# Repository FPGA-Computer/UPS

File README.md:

UPS
===

This is the repository for my Switch Mode Power Supply modules & UPS schematic/PCB files.

Schematic tool: Eagle CAD 6.5.0
3D modelling: Sketchup 14.1 2014

Due to components availability, UPS design is provided as is.

Project page:
https://hw-by-design.blogspot.com/2018/08/vrm-power-supply-modules.html
http://hw-by-design.blogspot.com/2018/08/vrm-discrete-33v-buck-converter.html
http://hw-by-design.blogspot.com/2018/08/emergency-backup-power-and-wallwarts.html

Licensing:
Schematic: Creative Commons 4.0 Attribution-ShareAlike 4.0 International
PCB & Layout: Creative Commons 4.0 Attribution-NonCommercial
3D modelling: Creative Commons 4.0 Attribution-ShareAlike 4.0 International

Creative Commons 4.0 Attribution-NonCommercial:
See http://creativecommons.org/licenses/by-nc/4.0/

Creative Commons 4.0 Attribution-ShareAlike 4.0 International
See http://creativecommons.org/licenses/by-sa/4.0/

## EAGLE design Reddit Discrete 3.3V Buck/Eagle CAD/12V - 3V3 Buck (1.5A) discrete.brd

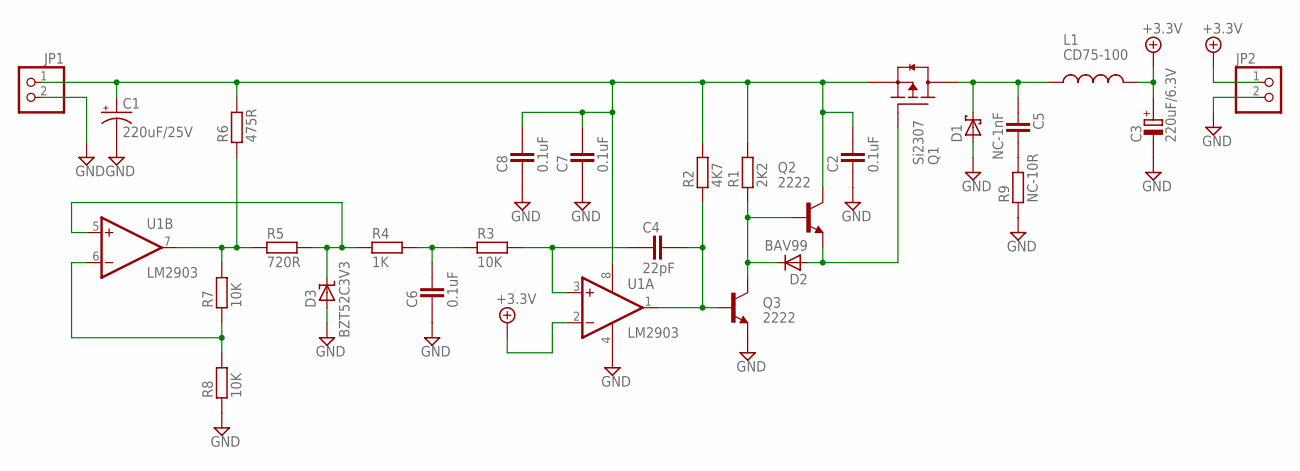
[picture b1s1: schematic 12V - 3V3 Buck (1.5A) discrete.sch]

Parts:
C1: 220uF/25V; PANASONIC_G
C2: 0.1uF; CAPC2012X145AN
C3: 220uF/6.3V; CAPMP7343X310N
C4: 22pF; CAPC1608X92N
C5: NC-1nF; CAPC1608X92N
C6, C7, C8: 0.1uF; CAPC1608X92N
D1: SCHOTTKY_SMC; DIOM7959X265N
D2: BAV99; SOT95P280X135-3N
D3: BZT52C3V3; SOD2514X100N
JP1, JP2: PINHD-1X2_2.54; 1X02
L1: CD75-100; CD75
Q1: Si2307; SOT95P280X135-3N
Q2, Q3: 2222; SOT95P280X135-3N
R1: 2K2; RESC1608X55N
R2: 4K7; RESC1608X55N
R3: 10K; RESC3115X70N
R4: 1K; RESC1608X55N
R5: 720R; RESC1608X55N
R6: 475R; RESC1608X55N
R7, R8: 10K; RESC1608X55N
R9: NC-10R; RESC1608X55N
U1: LM2903; SO08

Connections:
+3.3V: C3.+, JP2.1, L1.2, U1.2 (-IN)
GND: C1.-, C2.1, C3.-, C6.1, C7.1, C8.1, D1.A, D3.A, JP1.2, JP2.2, Q3.2 (E), R8.1, R9.1, U1.4 (V-)
unnamed: D2.3 (K), Q2.1 (B), Q3.3 (C), R1.1
unnamed: D2.1 (A), Q1.1 (G), Q2.2 (E)
unnamed: C4.2, Q3.1 (B), R2.1, U1.1 (OUT)
unnamed: C4.1, R3.2, U1.3 (+IN)
unnamed: C6.2, R3.1, R4.2
unnamed: C5.2, R9.2
unnamed: C1.+, C2.2, C7.2, C8.2, JP1.1, Q1.2 (S), Q2.3 (C), R1.2, R2.2, R6.2, U1.8 (V+)
unnamed: R5.1, R6.1, R7.2, U1.7 (OUT)
unnamed: R7.1, R8.2, U1.6 (-IN)
unnamed: D3.K, R4.1, R5.2, U1.5 (+IN)
VO-L: C5.1, D1.K, L1.1, Q1.3 (D)

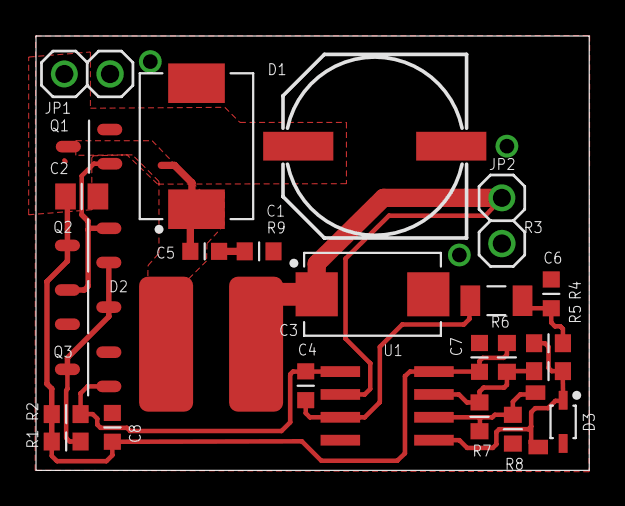
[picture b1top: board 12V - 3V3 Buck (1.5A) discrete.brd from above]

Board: 2 copper layers, 30.7 x 24.1 mm, 27 parts (0 on the bottom side), 13 nets.

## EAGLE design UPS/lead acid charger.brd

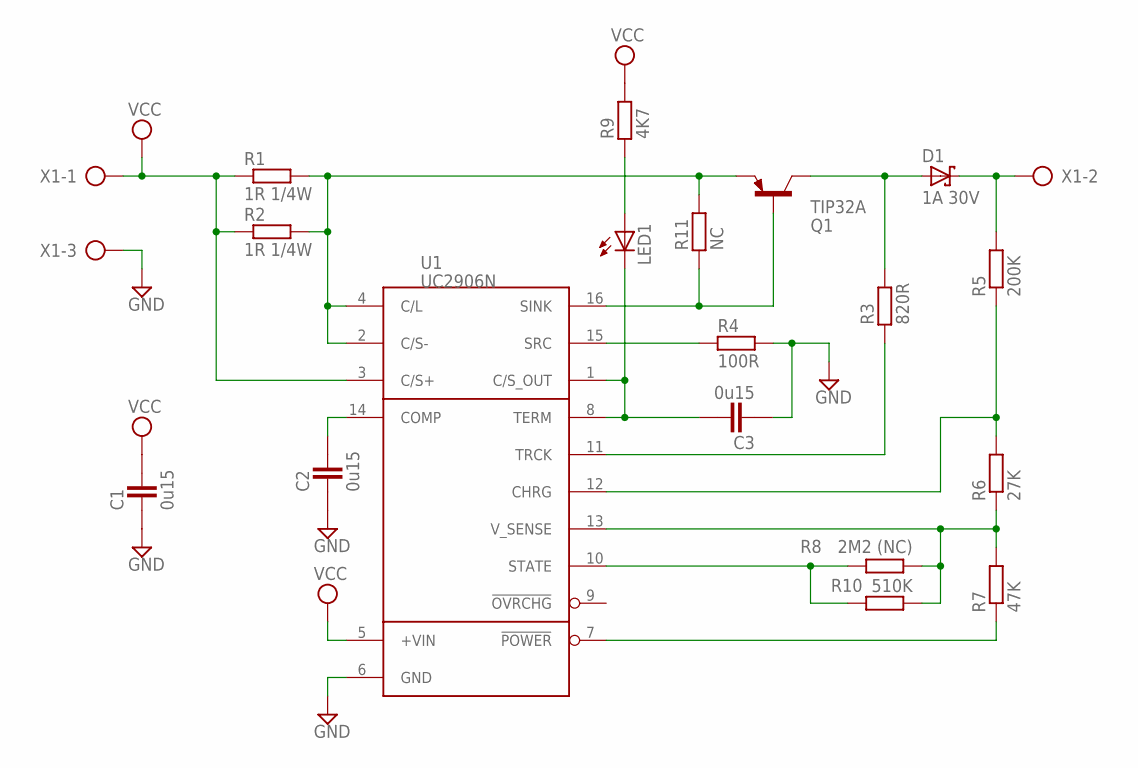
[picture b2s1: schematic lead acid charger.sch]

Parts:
C1, C2, C3: 0u15; CAP2012X70N
D1: 1A 30V; DIOM5436X265N
LED1: LED3MM
Q1: TIP32A; TO220
R1, R2: 1R 1/4W; 0207/10
R3: 820R; RESC3115X70N
R4: 100R; RESC2012X70N
R5: 200K; 0207/10
R6: 27K; 0207/10
R7: 47K; 0207/10
R8: 2M2 (NC); 0207/10
R9: 4K7; RESC2012X70N
R10: 510K; 0207/10
R11: NC; RESC1608X55N
U1: UC2906N; DIL16
X1: AK500/3; AK500-3

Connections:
GND: C1.1, C2.1, C3.1, R4.2, U1.6 (GND), X1.3
unnamed: C2.2, U1.14 (COMP)
unnamed: D1.K, R5.2, X1.2
unnamed: Q1.3 (E), R1.2, R2.2, R11.2, U1.2 (C/S-), U1.4 (C/L)
unnamed: C3.2, LED1.K (C), U1.1 (C/S_OUT), U1.8 (TERM)
unnamed: R7.1, U1.7 (!POWER)
unnamed: D1.A, Q1.2 (C), R3.2
unnamed: Q1.1 (B), R11.1, U1.16 (SINK)
unnamed: R3.1, U1.11 (TRCK)
unnamed: R4.1, U1.15 (SRC)
unnamed: R6.1, R7.2, R8.1, R10.1, U1.13 (V_SENSE)
unnamed: R5.1, R6.2, U1.12 (CHRG)
unnamed: R8.2, R10.2, U1.10 (STATE)
unnamed: LED1.A, R9.1
VCC: C1.2, R1.1, R2.1, R9.2, U1.3 (C/S+), U1.5 (+VIN), X1.1

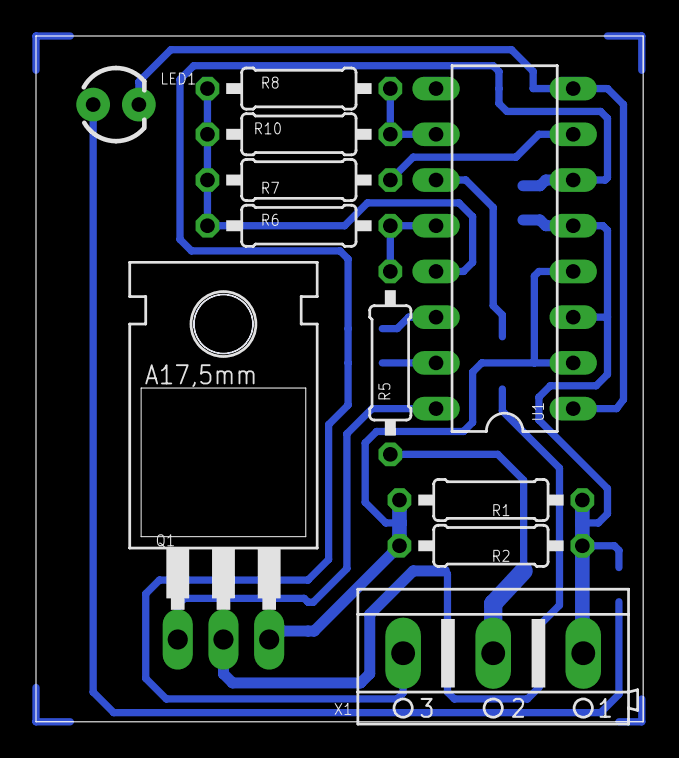
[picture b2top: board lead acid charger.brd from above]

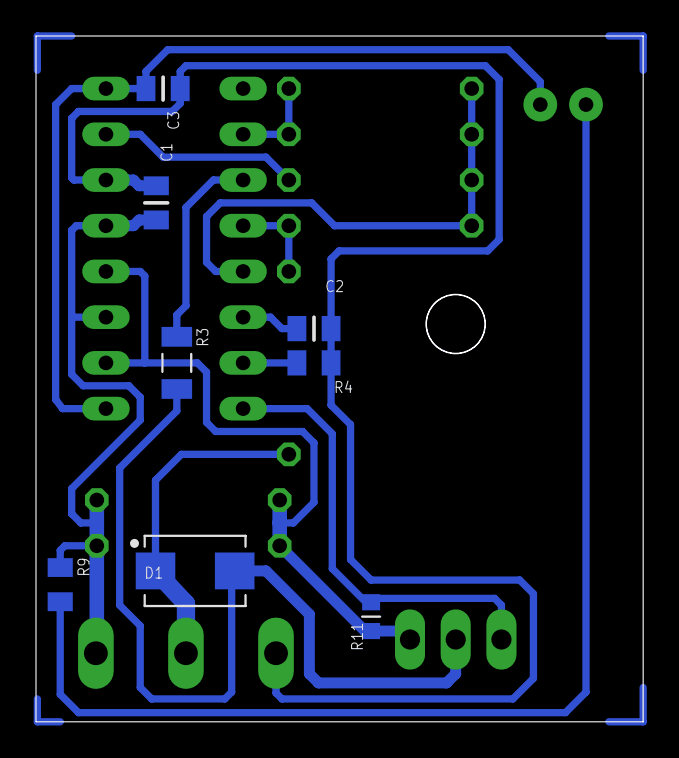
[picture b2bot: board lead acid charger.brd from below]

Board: 2 copper layers, 33.7 x 38.1 mm, 19 parts (8 on the bottom side), 15 nets.

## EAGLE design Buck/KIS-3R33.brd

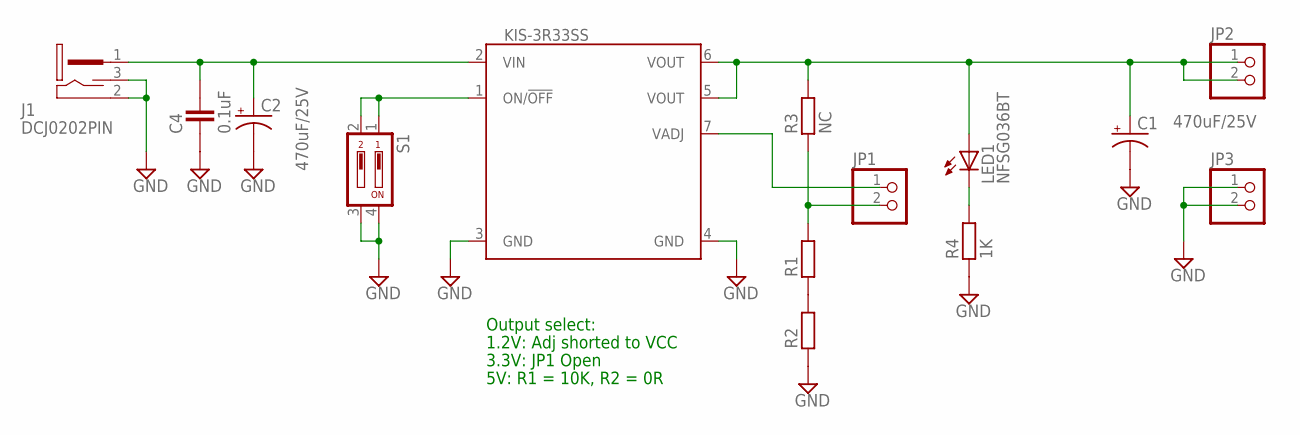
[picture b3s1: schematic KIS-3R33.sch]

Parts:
C1, C2: 470uF/25V; PANASONIC_G
C4: 0.1uF; CAP2012X70N
J1: DCJ0202PIN; PJ-102A
JP1: PINHD-1X2_2.54-SMD; 1X02SMD
JP2, JP3: PINHD-1X2_2.54; 1X02
LED1: NFSG036BT
R1, R2: RESISTOR_1206; RESC3115X70N
R3: NC; RESC3115X70N
R4: 1K; RESC1608X55N
S1: DIP02YL
U1: KIS-3R33SS; KIS-3R33S-SMT

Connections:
GND: C1.-, C2.-, C4.1, J1.2 (3), J1.3 (2), JP3.1, JP3.2, R2.1, R4.1, S1.3, S1.4, U1.3 (GND), U1.4 (GND)
unnamed: C1.+, JP2.1, JP2.2, LED1.A, R3.2, U1.5 (VOUT), U1.6 (VOUT)
unnamed: C2.+, C4.2, J1.1, U1.2 (VIN)
unnamed: JP1.1, U1.7 (VADJ)
unnamed: R1.1, R2.2
unnamed: JP1.2, R1.2, R3.1
unnamed: LED1.C, R4.2
unnamed: S1.1, S1.2, U1.1 (ON/!OFF)

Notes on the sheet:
5V: R1 = 10K, R2 = 0R
3.3V: JP1 Open
1.2V: Adj shorted to VCC
Output select:

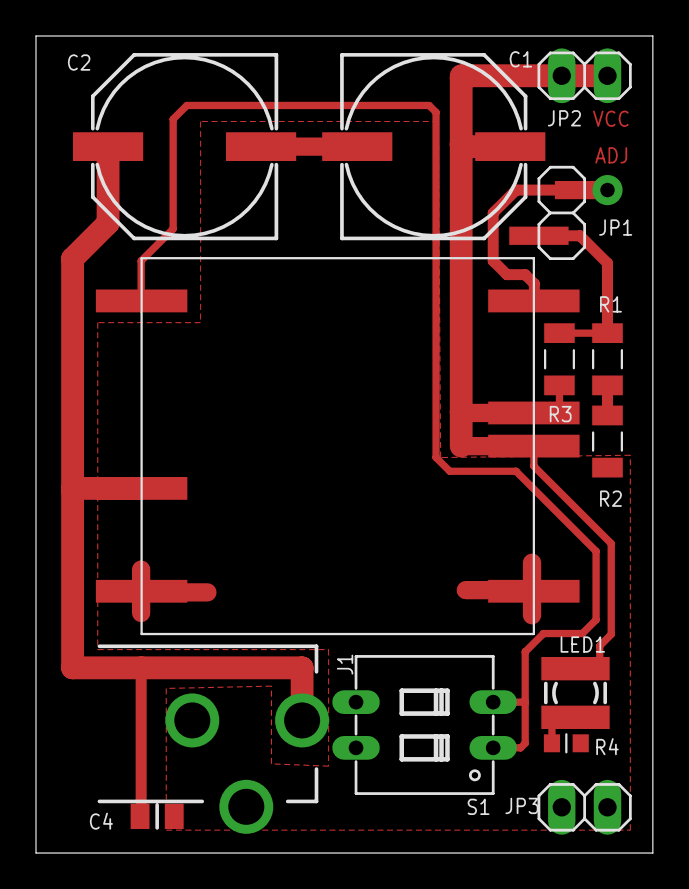
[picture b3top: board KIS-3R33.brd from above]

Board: 2 copper layers, 34.3 x 45.4 mm, 14 parts (0 on the bottom side), 8 nets.

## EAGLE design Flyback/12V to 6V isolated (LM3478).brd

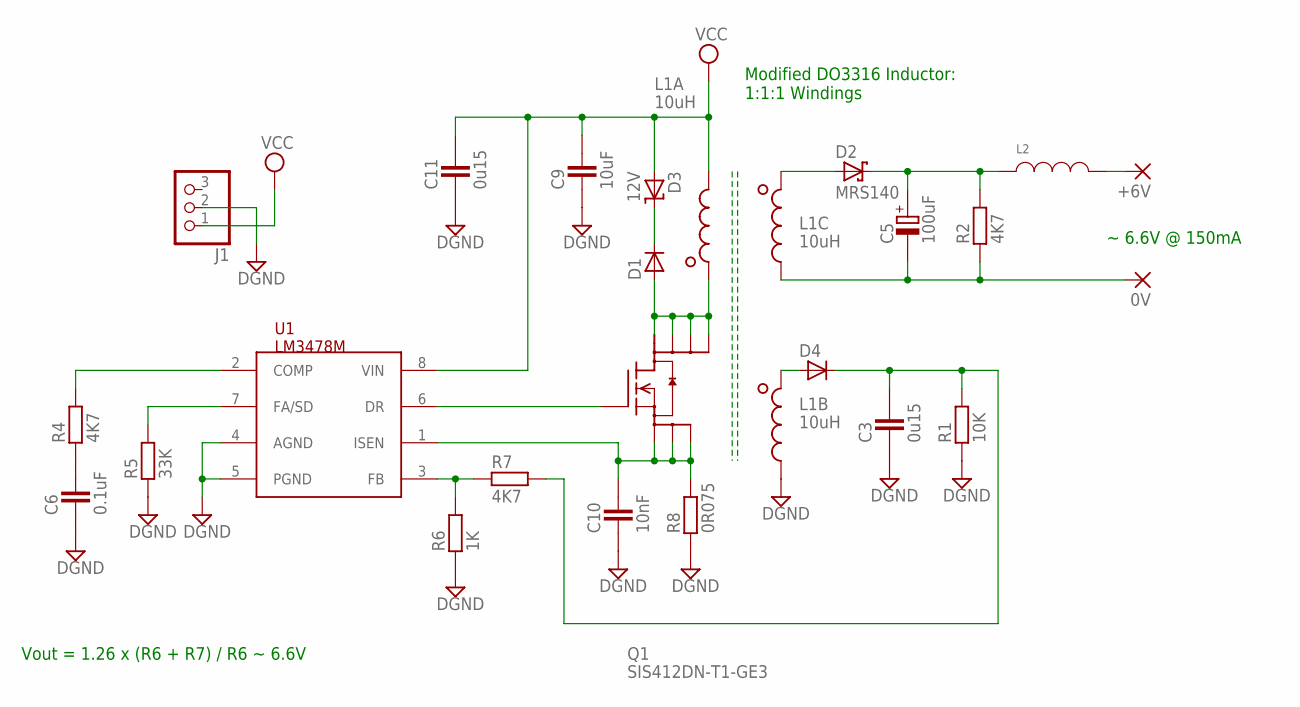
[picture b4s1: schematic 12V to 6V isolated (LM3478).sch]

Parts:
0V: SMD2; SMD1,27-2,54
+6V: SMD2; SMD1,27-2,54
C3, C11: 0u15; CAP2012X70N
C5: 100uF; CAPMP7343X310N
C6: 0.1uF; CAPC1608X92N
C9: 10uF; CAPC3225X168N
C10: 10nF; CAPC1608X92N
D1, D4: DIODE_SOT-23; SOT95P280X135-3N
D2: MRS140; DIOM5436X265N
D3: 12V; SOT95P280X135-3N
J1: PINHD-1X3; 1X03
L1: 10uH; DO3316P-3
L2: INDUCTOR_1812; INDC4532X175N
Q1: SIS412DN-T1-GE3; POWER-PAK1212
R1: 10K; RESC2012X70N
R2, R7: 4K7; RESC2012X70N
R4: 4K7; RESC1608X55N
R5: 33K; RESC1608X55N
R6: 1K; RESC2012X70N
R8: 0R075; RESC6432X70N
U1: LM3478M; MSOP8

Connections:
DGND: C3.1, C6.1, C9.1, C10.1, C11.1, J1.2, L1.4 (2), R1.1, R5.1, R6.1, R8.1, U1.4 (AGND), U1.5 (PGND)
unnamed: R4.2, U1.2 (COMP)
unnamed: D1.3 (K), D3.3 (K)
unnamed: C6.2, R4.1
unnamed: R5.2, U1.7 (FA/SD)
unnamed: D4.1 (A), L1.3 (1)
unnamed: Q1.4 (G), U1.6 (DR)
unnamed: C3.2, D4.3 (K), R1.2, R7.2
unnamed: C5.+, D2.K, L2.1, R2.2
unnamed: R6.2, R7.1, U1.3 (FB)
unnamed: 0V.1, C5.-, L1.6 (2), R2.1
unnamed: D1.1 (A), L1.1, Q1.5 (D1), Q1.6 (D2), Q1.7 (D3), Q1.8 (D4)
unnamed: D2.A, L1.5 (1)
unnamed: +6V.1, L2.2
unnamed: C10.2, Q1.1 (S1), Q1.2 (S2), Q1.3 (S3), R8.2, U1.1 (ISEN)
VCC: C9.2, C11.2, D3.1 (A), J1.1, L1.2, U1.8 (VIN)

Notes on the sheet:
Vout = 1.26 x (R6 + R7) / R6 ~ 6.6V
~ 6.6V @ 150mA
Modified DO3316 Inductor: 1:1:1 Windings

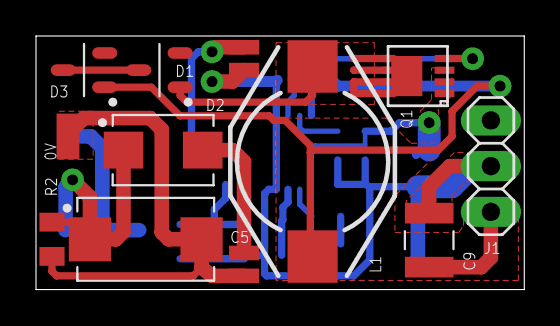
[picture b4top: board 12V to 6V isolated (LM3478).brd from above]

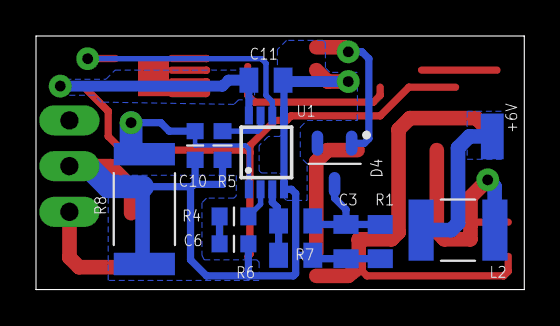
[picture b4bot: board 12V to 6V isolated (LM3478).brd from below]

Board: 2 copper layers, 27.1 x 14.1 mm, 24 parts (14 on the bottom side), 16 nets.

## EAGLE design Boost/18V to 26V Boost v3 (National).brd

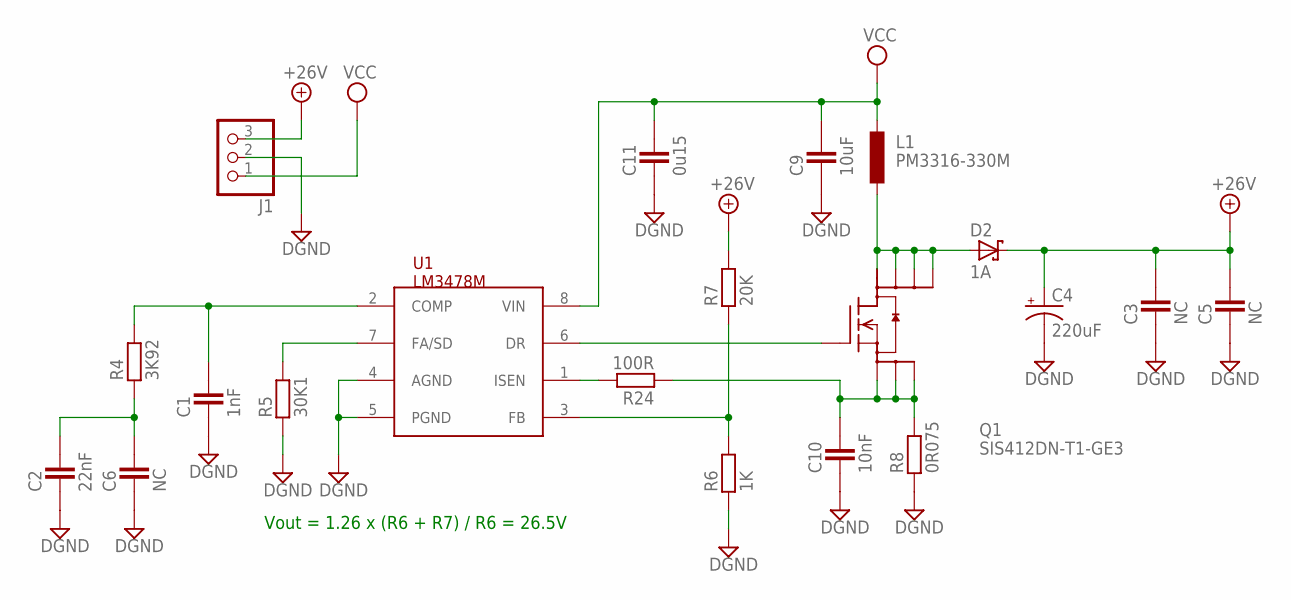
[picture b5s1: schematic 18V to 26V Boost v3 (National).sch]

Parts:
C1: 1nF; CAP2012X70N
C2: 22nF; CAPC1608X92N
C3, C5: NC; CAPC3225X168N
C4: 220uF; PANASONIC_G
C6: NC; CAPC1608X92N
C9: 10uF; CAPC3225X168N
C10: 10nF; CAPC1608X92N
C11: 0u15; CAP2012X70N
D2: 1A; DIOM5436X265N
J1: PINHD-1X3; 1X03
L1: PM3316-330M; DO3316P
Q1: SIS412DN-T1-GE3; POWER-PAK1212
R4: 3K92; RESC1608X55N
R5: 30K1; RESC1608X55N
R6: 1K; RESC1608X55N
R7: 20K; RESC1608X55N
R8: 0R075; RESC6432X70N
R24: 100R; RESC1608X55N
U1: LM3478M; MSOP08

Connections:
+26V: C3.2, C4.+, C5.2, D2.K, J1.3, R7.2
DGND: C1.1, C2.1, C3.1, C4.-, C5.1, C6.1, C9.1, C10.1, C11.1, J1.2, R5.1, R6.1, R8.1, U1.4 (AGND), U1.5 (PGND)
unnamed: C1.2, R4.2, U1.2 (COMP)
unnamed: C2.2, C6.2, R4.1
unnamed: R5.2, U1.7 (FA/SD)
unnamed: Q1.4 (G), U1.6 (DR)
unnamed: R6.2, R7.1, U1.3 (FB)
unnamed: C10.2, Q1.1 (S1), Q1.2 (S2), Q1.3 (S3), R8.2, R24.1
unnamed: D2.A, L1.2, Q1.5 (D1), Q1.6 (D2), Q1.7 (D3), Q1.8 (D4)
unnamed: R24.2, U1.1 (ISEN)
VCC: C9.2, C11.2, J1.1, L1.1, U1.8 (VIN)

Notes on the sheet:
Vout = 1.26 x (R6 + R7) / R6 = 26.5V

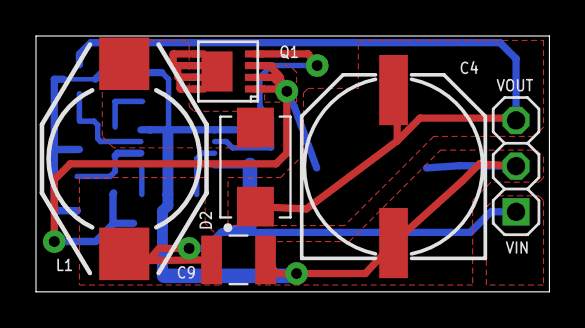
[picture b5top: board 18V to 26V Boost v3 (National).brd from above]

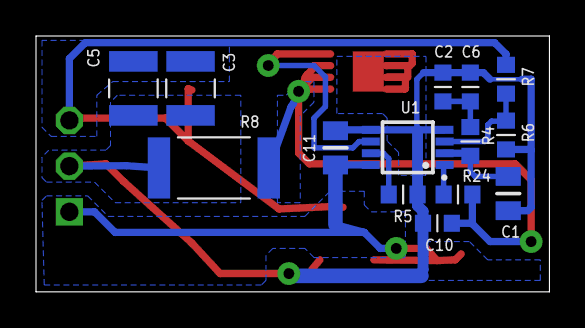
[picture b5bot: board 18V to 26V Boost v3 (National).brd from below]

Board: 2 copper layers, 28.5 x 14.2 mm, 20 parts (14 on the bottom side), 11 nets.

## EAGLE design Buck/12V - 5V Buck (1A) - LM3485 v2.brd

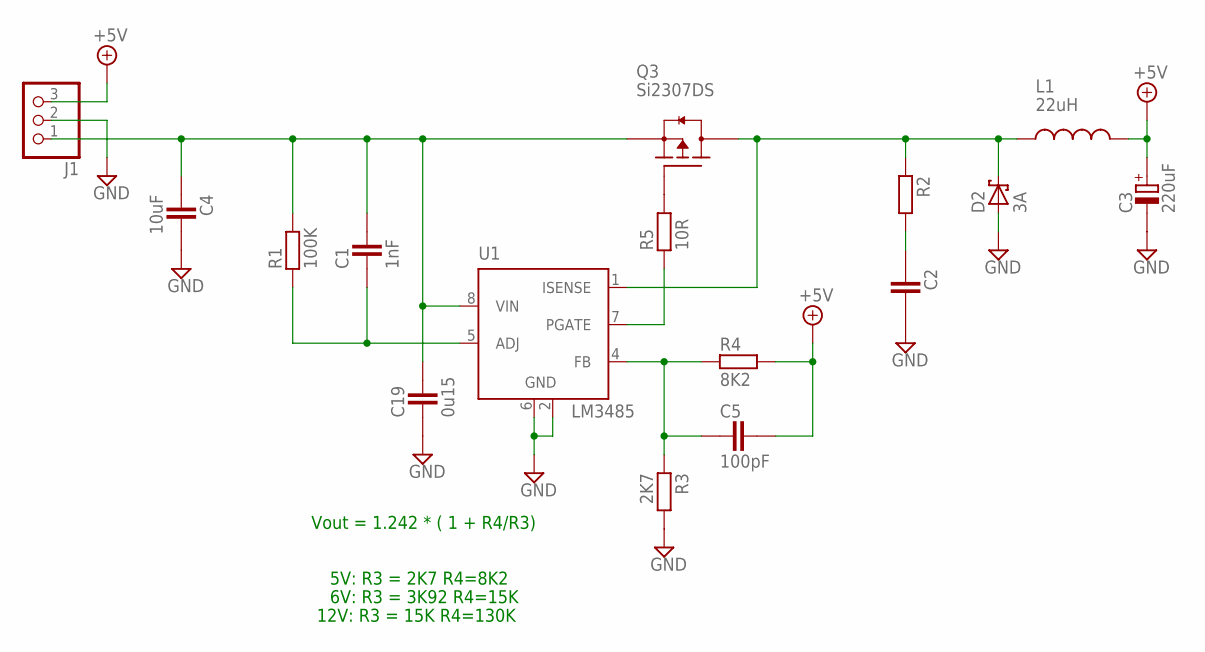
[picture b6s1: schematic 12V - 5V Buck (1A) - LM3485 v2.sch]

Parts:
C1: 1nF; CAP2012X70N
C2: CAPACITOR_0805N; CAP2012X70N
C3: 220uF; CAPMP7343X310N
C4: 10uF; CAPC3225X168N
C5: 100pF; CAP2012X70N
C19: 0u15; CAPC1608X92N
D2: 3A; DIOM7959X265N
J1: PINHD-1X3; 1X03
L1: 22uH; DO3316P
Q3: Si2307DS; SOT95P280X135-3N
R1: 100K; RESC1608X55N
R2: RESISTOR_0603; RESC1608X55N
R3: 2K7; RESC2012X70N
R4: 8K2; RESC2012X70N
R5: 10R; RESC1608X55N
U1: LM3485; MSOP08

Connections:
+5V: C3.+, C5.2, J1.3, L1.2, R4.2
+12V: C1.2, C4.1, C19.2, J1.1, Q3.2 (S), R1.2, U1.8 (VIN)
GND: C2.2, C3.-, C4.2, C19.1, D2.A, J1.2, R3.2, U1.2 (GND), U1.6 (GND)
unnamed: C5.1, R3.1, R4.1, U1.4 (FB)
unnamed: R5.1, U1.7 (PGATE)
unnamed: C1.1, R1.1, U1.5 (ADJ)
unnamed: C2.1, R2.2
unnamed: Q3.1 (G), R5.2
VO-L: D2.K, L1.1, Q3.3 (D), R2.1, U1.1 (ISENSE)

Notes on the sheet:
Vout = 1.242 * ( 1 + R4/R3)
5V: R3 = 2K7 R4=8K2
12V: R3 = 15K R4=130K
6V: R3 = 3K92 R4=15K

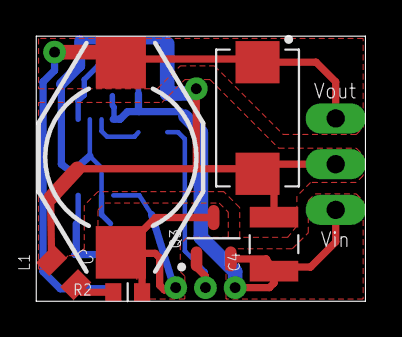
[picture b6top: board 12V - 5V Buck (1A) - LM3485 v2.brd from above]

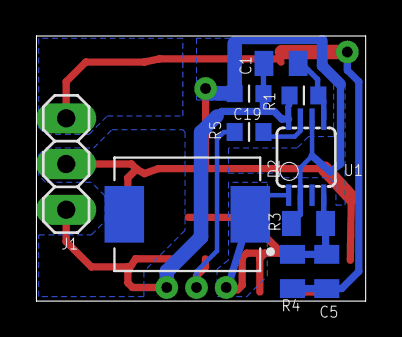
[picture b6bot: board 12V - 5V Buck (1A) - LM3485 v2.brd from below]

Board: 2 copper layers, 18.3 x 14.7 mm, 16 parts (10 on the bottom side), 9 nets.

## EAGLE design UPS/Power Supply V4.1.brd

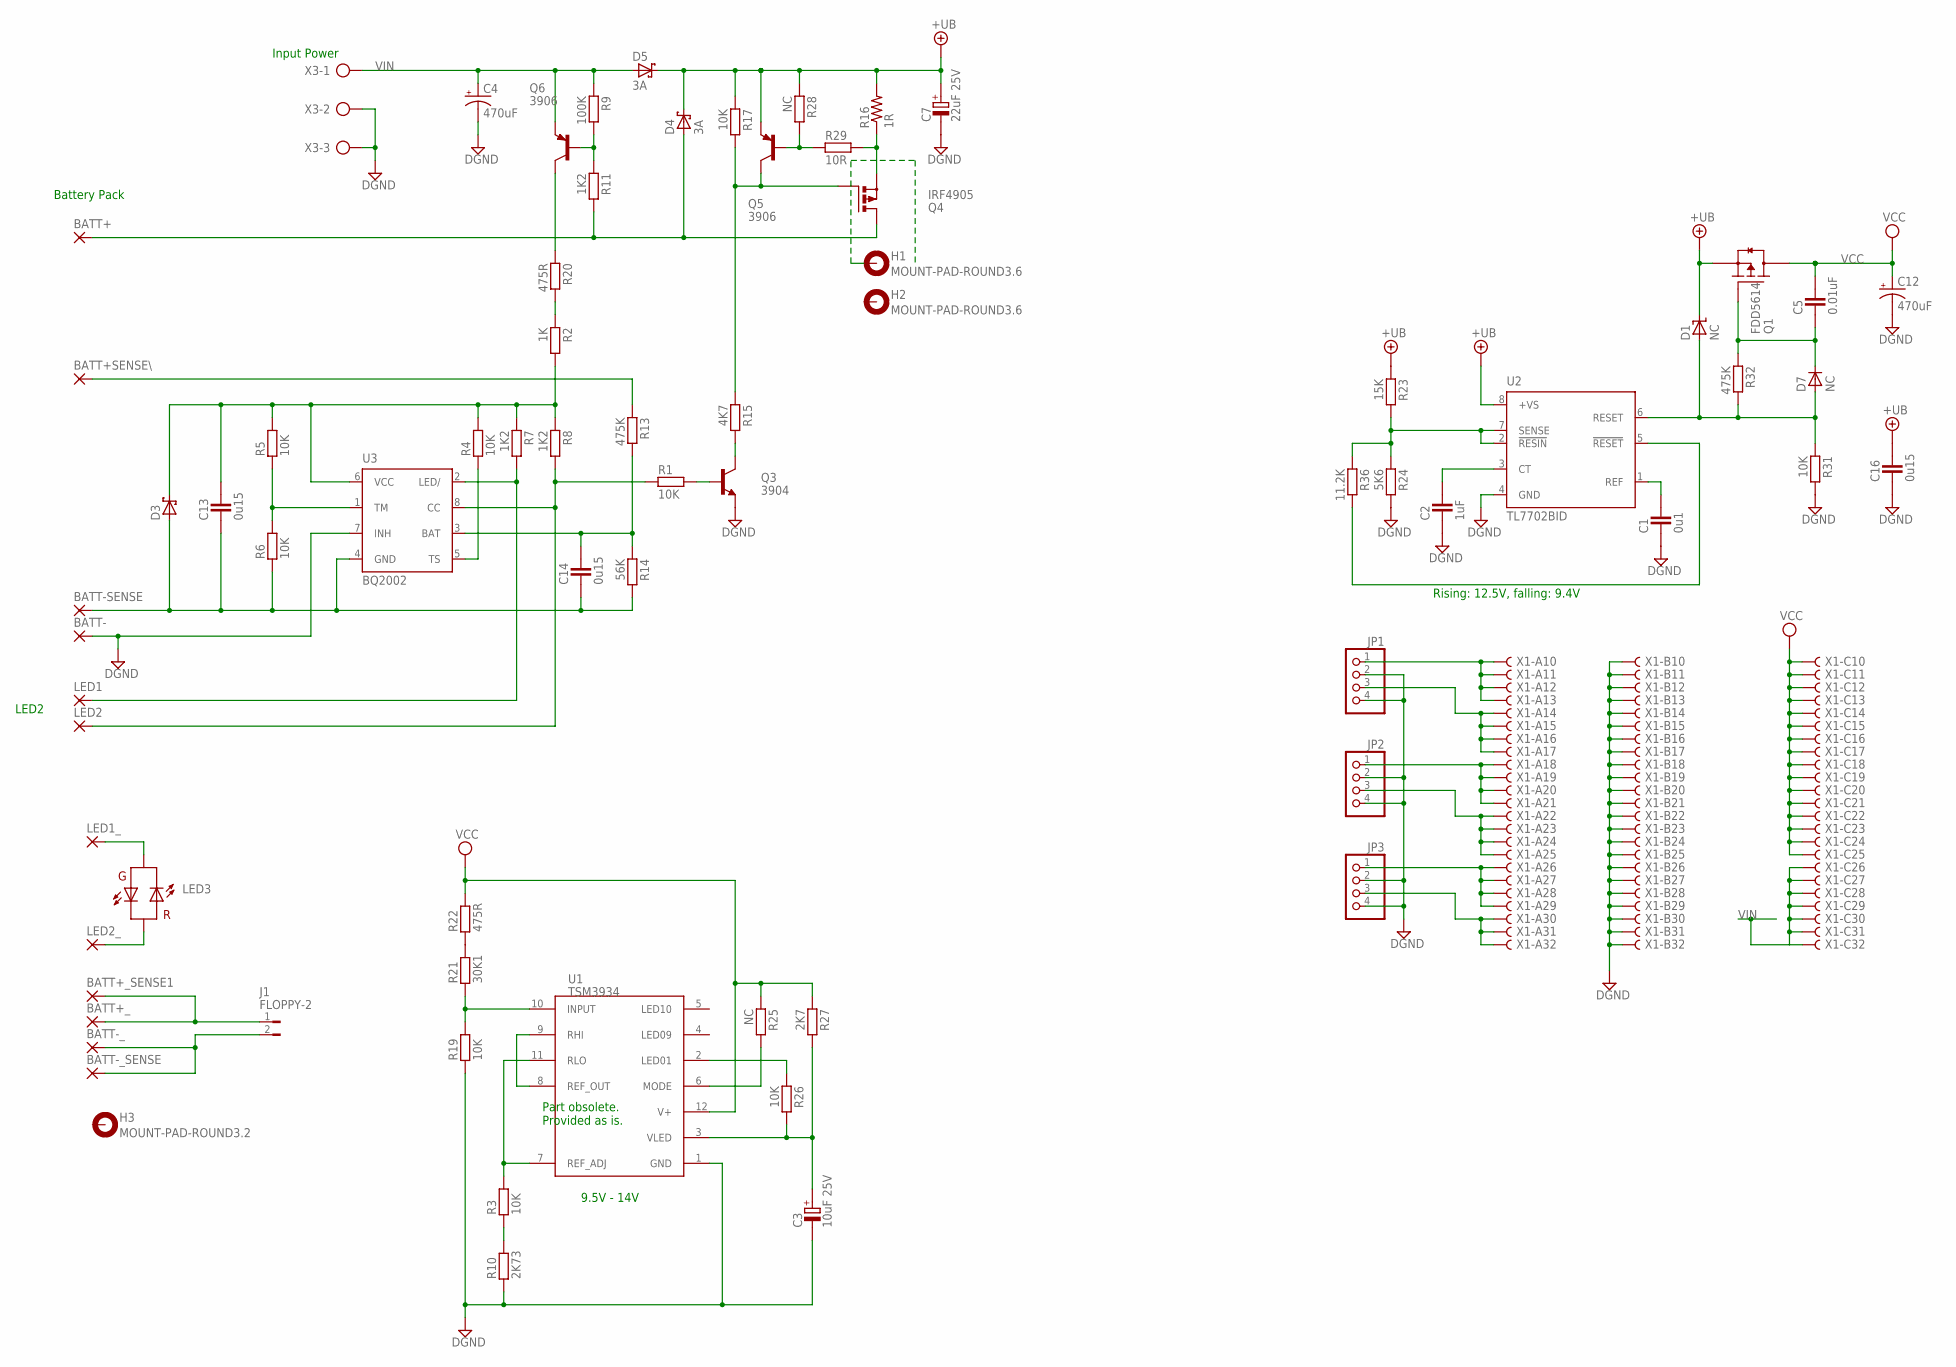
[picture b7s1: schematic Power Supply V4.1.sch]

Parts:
BATT+: SMD5; SMD2,54-5,08
BATT+SENSE\: SMD5; SMD2,54-5,08
BATT+_: SMD5; SMD2,54-5,08
BATT+_SENSE1: SMD5; SMD2,54-5,08
BATT-: SMD5; SMD2,54-5,08
BATT-SENSE: SMD5; SMD2,54-5,08
BATT-_: SMD5; SMD2,54-5,08
BATT-_SENSE: SMD5; SMD2,54-5,08
C1: 0u1; CAPC1608X92N
C2: 1uF; CAPC1608X92N
C3: 10uF 25V; CAPMP7343X310N
C4, C12: 470uF; PANASONIC_G
C5: 0.01uF; CAP2012X70N
C7: 22uF 25V; CAPMP7343X310N
C13, C14, C16: 0u15; CAPC1608X92N
D1, D7: NC; SOT95P280X135-3N
D3: SCHOTTKY_SOT-23; SOT95P280X135-3N
D4, D5: 3A; DIOM7959X265N
H1, H2: MOUNT-PAD-ROUND3.6; 3,6-PAD
H3: MOUNT-PAD-ROUND3.2; 3,2-PAD
J1: FLOPPY-2
JP1, JP2, JP3: PINHD-1X4_2.54; 1X04
LED1, LED1_, LED2, LED2_: SMD5; SMD2,54-5,08
LED3: DUAL-LED3MM; LED3MM
Q1: FDD5614; D-PAK_TO252AA
Q3: 3904; SOT95P280X135-3N
Q4: IRF4905; TO220BH
Q5, Q6: 3906; SOT95P280X135-3N
R1, R3, R4, R5, R6, R17, R19, R26, R31: 10K; RESC1608X55N
R2: 1K; RESC2012X70N
R7, R8, R11: 1K2; RESC1608X55N
R9: 100K; RESC1608X55N
R10: 2K73; RESC1608X55N
R13, R32: 475K; RESC1608X55N
R14: 56K; RESC2012X70N
R15: 4K7; RESC1608X55N
R16: 1R; 0411/12
R20: 475R; RESC2012X70N
R21: 30K1; RESC1608X55N
R22: 475R; RESC1608X55N
R23: 15K; RESC2012X70N
R24: 5K6; RESC2012X70N
R25, R28: NC; RESC1608X55N
R27: 2K7; RESC1608X55N
R29: 10R; RESC1608X55N
R36: 11.2K; RESC1608X55N
U1: TSM3934
U2: TL7702BID; SO08
U3: BQ2002; DIL08
X1: FABC69R
X3: AK500/3

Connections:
+UB: C7.+, C16.2, D1.3 (K), D4.K, D5.K, Q1.3 (S), Q5.2 (E), R16.2, R17.1, R23.1, R28.1, U2.8 (+VS)
DGND: BATT-.1, C1.1, C2.1, C3.-, C4.-, C7.-, C12.-, C16.1, JP1.2, JP1.4, JP2.2, JP2.4, JP3.2, JP3.4, Q3.2 (E), R10.1, R19.1, R24.2, R31.2, U1.1 (GND), U2.4 (GND), U3.7 (INH), X1.B10, X1.B11, X1.B12, X1.B13, X1.B14, X1.B15, X1.B16, X1.B17, X1.B18, X1.B19, X1.B20, X1.B21, X1.B22, X1.B23, X1.B24, X1.B25, X1.B26, X1.B27, X1.B28, X1.B29, X1.B30, X1.B31, X1.B32, X3.2, X3.3
unnamed: R23.2, R24.1, R36.1, U2.2 (!RESIN), U2.7 (SENSE)
unnamed: Q3.1 (B), R1.2
unnamed: R2.1, R20.2
unnamed: Q6.3 (C), R20.1
unnamed: C2.2, U2.3 (CT)
unnamed: C13.2, D3.3 (K), R2.2, R4.2, R5.2, R7.1, R8.1, U3.6 (VCC)
unnamed: C1.2, U2.1 (REF)
unnamed: R36.2, U2.5 (!RESET)
unnamed: LED2.1, R1.1, R8.2, U3.8 (CC)
unnamed: C5.1, D7.3 (K), Q1.1 (G), R32.1
unnamed: R4.1, U3.5 (TS)
unnamed: C14.2, R13.2, R14.1, U3.3 (BAT)
unnamed: R3.2, U1.7 (REF_ADJ), U1.11 (RLO)
unnamed: Q3.3 (C), R15.2
unnamed: Q4.G, Q5.3 (C), R15.1, R17.2
unnamed: Q4.S, R16.1, R29.2
unnamed: BATT+.1, D4.A, Q4.D, R11.2
unnamed: D1.1 (A), D7.1 (A), R31.1, R32.2, U2.6 (RESET)
unnamed: U1.8 (REF_OUT), U1.9 (RHI)
unnamed: Q6.1 (B), R9.2, R11.1
unnamed: R21.2, R22.1
unnamed: R5.1, R6.2, U3.1 (TM)
unnamed: LED1.1, R7.2, U3.2 (LED/)
unnamed: R19.2, R21.1, U1.10 (INPUT)
unnamed: R3.1, R10.2
unnamed: BATT+SENSE\.1, R13.1
unnamed: LED1_.1, LED3.A
unnamed: C3.+, R26.2, R27.2, U1.3 (VLED)
unnamed: LED2_.1, LED3.K (C)
unnamed: R25.2, U1.6 (MODE)
unnamed: BATT-_.1, BATT-_SENSE.1, J1.2
unnamed: R26.1, U1.2 (LED01)
unnamed: BATT+_.1, BATT+_SENSE1.1, J1.1
unnamed: Q5.1 (B), R28.2, R29.1
unnamed: JP1.1, X1.A10, X1.A11, X1.A12, X1.A13
unnamed: JP1.3, X1.A14, X1.A15, X1.A16, X1.A17
unnamed: JP2.1, X1.A18, X1.A19, X1.A20, X1.A21
unnamed: JP2.3, X1.A22, X1.A23, X1.A24, X1.A25
unnamed: JP3.1, X1.A26, X1.A27, X1.A28, X1.A29
unnamed: JP3.3, X1.A30, X1.A31, X1.A32
unnamed: BATT-SENSE.1, C13.1, C14.1, D3.1 (A), R6.1, R14.2, U3.4 (GND)
VCC: C5.2, C12.+, Q1.4 (D), R22.2, R25.1, R27.1, U1.12 (V+), X1.C10, X1.C11, X1.C12, X1.C13, X1.C14, X1.C15, X1.C16, X1.C17, X1.C18, X1.C19, X1.C20, X1.C21, X1.C22, X1.C23, X1.C24, X1.C25
VIN: C4.+, D5.A, Q6.2 (E), R9.1, X1.C26, X1.C27, X1.C28, X1.C29, X1.C30, X1.C31, X1.C32, X3.1

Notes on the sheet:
Input Power
Battery Pack
LED2
9.5V - 14V
Rising: 12.5V, falling: 9.4V
Part obsolete. Provided as is.

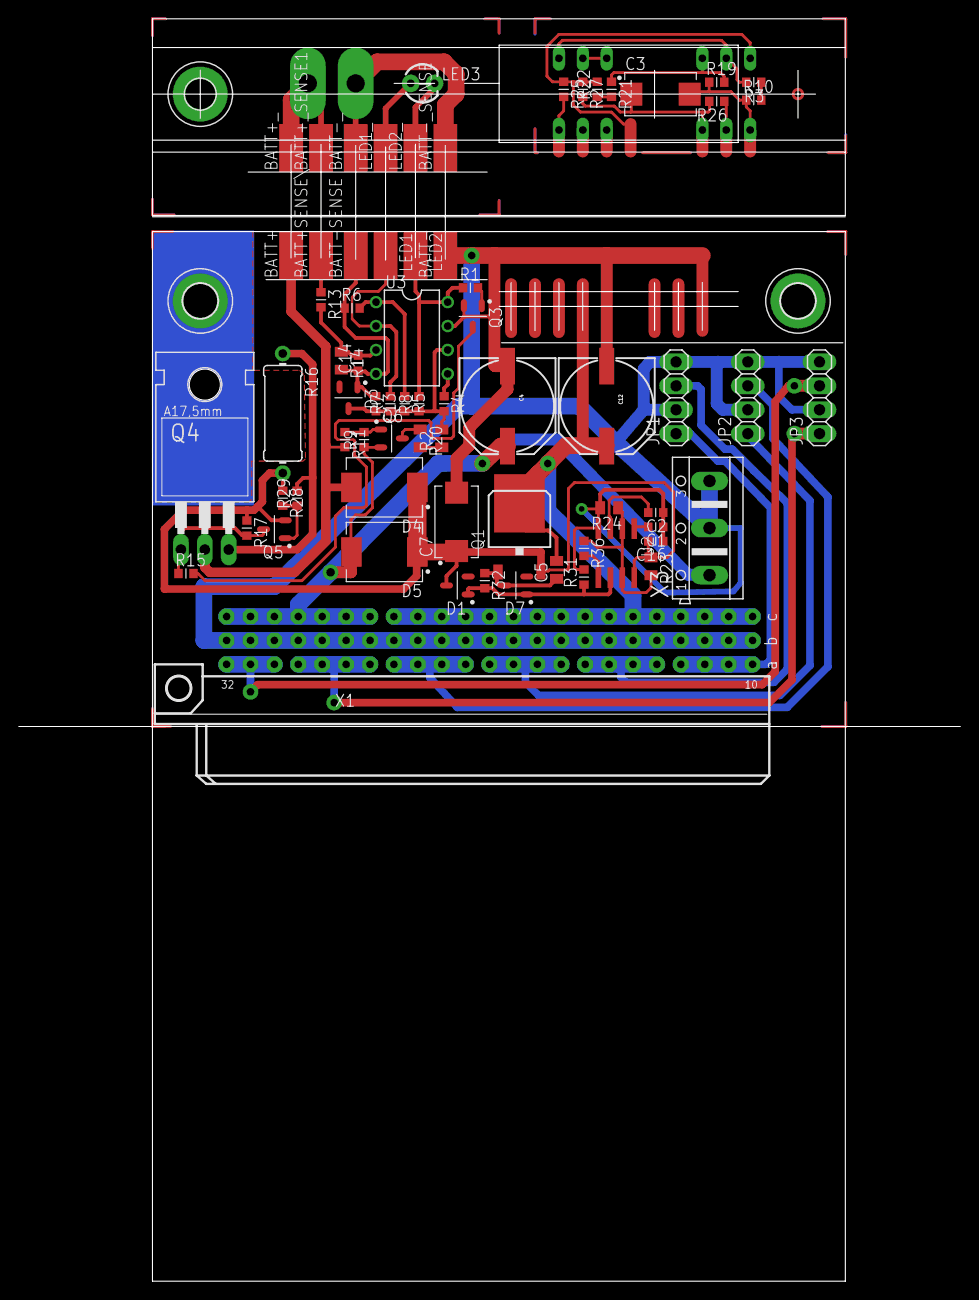
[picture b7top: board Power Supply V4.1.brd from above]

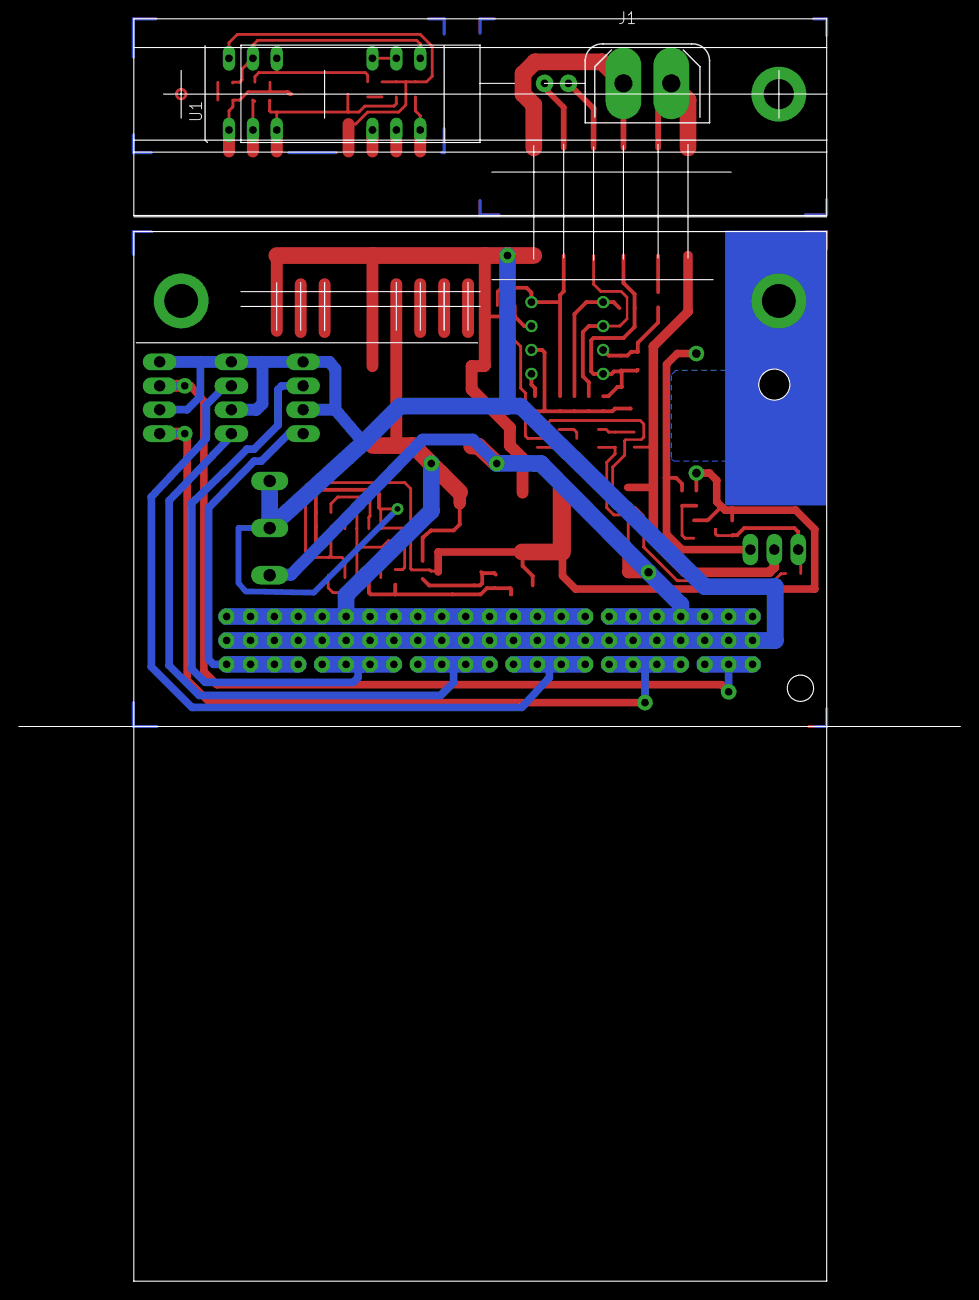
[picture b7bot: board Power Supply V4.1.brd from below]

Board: 2 copper layers, 100.0 x 134.1 mm, 75 parts (2 on the bottom side), 45 nets.

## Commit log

2015-06-13 Added lead acid charger
2015-08-07 Relax license
2015-08-07 Remove datasheets
2016-07-05 Add Reddit challenge 3.3V Buck
2016-07-05 Added project page
2018-08-02 Update project hosting, added discrete 10A sync buck converter
